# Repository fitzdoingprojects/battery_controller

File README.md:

# battery_controller
battery_controller

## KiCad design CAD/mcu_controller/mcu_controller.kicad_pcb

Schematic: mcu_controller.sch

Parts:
C1, C3: 10uF 50V; C_1206_3216Metric
C2: 0.1uF; C_0603_1608Metric
D1, D3: LED_Small; LED_0603_1608Metric
D2: TL431DBZ; SOT-23
J1: BATT; PhoenixContact_MCV_1,5_2-G-5.08_1x02_P5.08mm_Vertical
J2: BATT_SENSE; PhoenixContact_MCV_1,5_2-G-5.08_1x02_P5.08mm_Vertical
J3: chrg1_vi; PinSocket_1x03_P2.54mm_Vertical
J4: chrg2_vi; PinSocket_1x03_P2.54mm_Vertical
J5: chrg3_vi; PinSocket_1x03_P2.54mm_Vertical
J6: out1_fb; PinSocket_1x05_P2.54mm_Vertical
J7: out2_fb; PinSocket_1x05_P2.54mm_Vertical
J9: out1_ch_en; PinSocket_1x05_P2.54mm_Vertical
J10: out2_ch_en; PinSocket_1x05_P2.54mm_Vertical
J11: SPI; PinSocket_1x05_P2.54mm_Vertical
J12: I2C; PinSocket_1x04_P2.54mm_Vertical
J13: chrg1_ctrl; PinSocket_1x04_P2.54mm_Vertical
J14: chrg2_ctrl; PinSocket_1x04_P2.54mm_Vertical
J15: chrg3_ctrl; PinSocket_1x04_P2.54mm_Vertical
J16: out1_en; PinSocket_1x02_P2.54mm_Vertical
J17: out2_en; PinSocket_1x02_P2.54mm_Vertical
J19: UART; PinSocket_1x04_P2.54mm_Vertical
J20: UEXT; PinSocket_2x05_P2.54mm_Vertical
JP1, JP2: Jumper_NC_Small; SolderJumper-2_P1.3mm_Bridged_RoundedPad1.0x1.5mm
MK1, MK2, MK3, MK4: Mounting_Hole; MountingHole_4.3mm_M4
R1, R2, R24: R; R_0603_1608Metric
R3, R4, R5, R6, R8, R10, R11, R12, R14, R17: 100; R_0603_1608Metric
R7, R9, R15, R18: 100; SolderJumper-2_P1.3mm_Open_RoundedPad1.0x1.5mm
R13, R16, R19, R20, R21, R22, R23, R25, R26, R27, R36: R_Small; R_0603_1608Metric
R28, R29, R30, R31, R32, R33, R34, R35: 1K; SolderJumper-2_P1.3mm_Open_RoundedPad1.0x1.5mm
R37, R38, R39, R40, R41, R42, R43, R44, R45, R46, R47: 1K; R_0603_1608Metric
SW1: SW_SPST; PinSocket_1x02_P2.54mm_Vertical
U1: INA219; SOIC-8_3.9x4.9mm_P1.27mm
U2: AZ1117-ADJ; SOT-223-3_TabPin2
U3: Teensy-LC; Teensy30_31_32_LC

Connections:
+5V: C2.1, C3.1, D1.2, R16.1, R19.1, R21.1, R25.1, R27.1, U1.4, U2.2 (VO), U3.33
/3V3: J11.1, J12.1, J19.1, J20.1, U3.31
/A0: R3.1, U3.21
/A1: R10.2, U3.22
/A2: R4.1, U3.23
/A3: R11.2, U3.24
/A4: JP2.2, U3.25
/A5: JP1.2, U3.26
/A6: R5.1, U3.27
/A7: R12.2, U3.28
/A8: R6.1, U3.29
/A9: R8.1, U3.30
/BATT_IN: J1.2, SW1.1
/BATT_SW: C1.1, R1.1, SW1.2, U2.3 (VI)
/I2C_SCL: J12.2, J20.5, JP1.1, U1.6
/I2C_SDA: J12.3, J20.6, JP2.1, U1.5
/MISO: J11.3, J20.7, U3.14
/MOSI: J11.2, J20.8, U3.13
/RESET: J20.10, U3.18
/RX: J19.3, J20.4, U3.2
/SCK: J11.4, J20.9, U3.20
/TX: J19.2, J20.3, U3.3
/chrg1_en: J13.1, R37.1
/chrg1_i: J3.2, R10.1
/chrg1_v: J3.3, R3.2
/chrg2_en: J14.1, R38.1
/chrg2_i: J4.2, R11.1
/chrg2_v: J4.3, R4.2
/chrg3_en: J15.1, R39.1
/chrg3_i: J5.2, R12.1
/chrg3_v: J5.3, R5.2
/mcu1_set: J13.3, R45.1
/mcu2_set: J14.3, R46.1
/mcu3_set: J15.3, R47.1
/out1_ch1_en: J9.1, R28.1
/out1_ch1_i: J6.1, R6.2
/out1_ch2_en: J9.2, R29.1
/out1_ch2_i: J6.2, R8.2
/out1_ch3_en: J9.3, R30.1
/out1_ch3_i: J6.3, R14.2
/out1_ch4_en: J9.4, R31.1
/out1_ch4_i: J6.4, R17.2
/out1_en: J16.1, R43.1
/out2_ch1_en: J10.1, R32.1
/out2_ch1_i: J7.1, R7.2
/out2_ch2_en: J10.2, R33.1
/out2_ch2_i: J7.2, R9.2
/out2_ch3_en: J10.3, R34.1
/out2_ch3_i: J7.3, R15.2
/out2_ch4_en: J10.4, R35.1
/out2_ch4_i: J7.4, R18.2
/out2_en: J17.1, R44.1
/trickle1_dis: J13.2, R40.1
/trickle2_dis: J14.2, R41.1
/trickle3_dis: J15.2, R42.1
GND: C1.2, C2.2, C3.2, D2.3, J1.1, J3.1, J4.1, J5.1, J6.5, J7.5, J9.5, J10.5, J11.5, J12.4, J13.4, J14.4, J15.4, J16.2, J17.2, J19.4, J20.2, R2.2, R13.1, R20.2, R22.2, R23.2, R26.2, R36.2, U1.3, U3.1, U3.17, U3.32
unnamed: D1.1, R23.1
unnamed: D2.1, R27.2, U3.35
unnamed: D2.2, R25.2, R26.1
unnamed: D3.1, R36.1
unnamed: D3.2, R43.2, R44.2, U3.4
unnamed: J2.1, U1.2
unnamed: J2.2, U1.1
unnamed: R1.2, R2.1, R24.1
unnamed: R13.2, R16.2, U2.1 (ADJ)
unnamed: R14.1, U3.36
unnamed: R17.1, R24.2, U3.37
unnamed: R19.2, R20.1, U1.8
unnamed: R21.2, R22.1, U1.7
unnamed: R37.2, U3.10
unnamed: R38.2, U3.8
unnamed: R39.2, U3.6
unnamed: R40.2, U3.9
unnamed: R41.2, U3.7
unnamed: R42.2, U3.5
unnamed: R45.2, U3.19
unnamed: R46.2, U3.12
unnamed: R47.2, U3.11

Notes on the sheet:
CHARGE CONTROLLER: 2x ADC 1x PWM 2x GPIO
OUTPUT CONTROLLER 4x ADC 1x (5x) GPIO

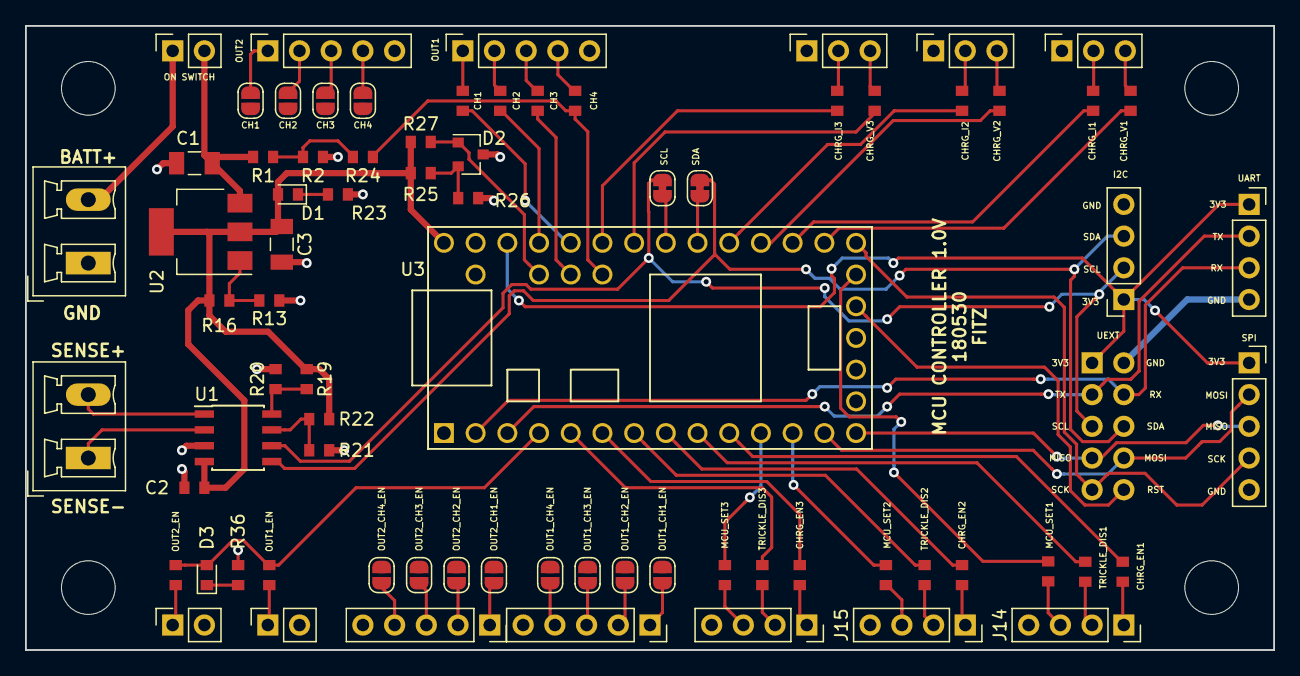
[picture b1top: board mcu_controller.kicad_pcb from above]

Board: 2 copper layers, 100.0 x 50.0 mm, 81 parts (1 on the bottom side), 78 nets.

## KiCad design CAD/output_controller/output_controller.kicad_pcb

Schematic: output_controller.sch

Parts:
C1: 10uF 25V; C_1206_3216Metric
C2, C3, C4, C5: 0.1uF; C_0603_1608Metric
D1: D_Small; D_SOD-523
D2: 12V; D_SOD-523
D3: LED_Small; D_SOD-523
D4, D5, D6, D7: 5V; D_SOD-323_HandSoldering
F1: Fuse; Fuseholder_Blade_Mini_Keystone_3568
J1: 12V_IN; PhoenixContact_MCV_1,5_2-G-5.08_1x02_P5.08mm_Vertical
J2: MCU_SW; PinHeader_1x02_P2.54mm_Vertical
J3: MCU_EN; PinHeader_1x05_P2.54mm_Vertical
J4: MCU_IS; PinHeader_1x05_P2.54mm_Vertical
J5, J6, J7, J8: 12V_A; PhoenixContact_MCV_1,5_2-G-5.08_1x02_P5.08mm_Vertical
MK1, MK2, MK3, MK4: Mounting_Hole; MountingHole_4.3mm_M4
Q1, Q3: Q_PMOS_GDS; TO-252-2
Q2: MMBT3904; SOT-23
Q4, Q5, Q6, Q7: AO3400; SOT-23
R1, R10, R11, R12, R13, R27, R29, R31, R33: 10K; R_0603_1608Metric
R2, R3, R5, R6, R7, R8, R9, R14, R15, R16, R17, R18, R19, R20, R21, R22, R23, R24, R25, R26, R28, R30, R32, R34: 1K; R_0603_1608Metric
R4: 470K; R_0603_1608Metric
SW1: EN; PinHeader_1x02_P2.54mm_Vertical
SW2, SW3, SW4, SW5: SW_Push_LED; PinHeader_1x04_P2.54mm_Vertical
U1, U2, U3, U4: BTS443P; TO-252-4

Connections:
/IN1: R15.1, U1.2 (IN)
/IN2: R16.1, U2.2 (IN)
/IN3: R17.1, U3.2 (IN)
/IN4: R18.1, U4.2 (IN)
/IN_SW1: C2.1, Q4.3, R15.2, SW2.2
/IN_SW2: C3.1, Q5.3, R16.2, SW3.2
/IN_SW3: C4.1, Q6.3, R17.2, SW4.2
/IN_SW4: C5.1, Q7.3, R18.2, SW5.2
/IS1: R23.1, R27.2, R28.2, U1.4 (IS)
/IS2: R24.1, R29.2, R30.2, U2.4 (IS)
/IS3: R25.1, R31.2, R32.2, U3.4 (IS)
/IS4: R26.1, R33.2, R34.2, U4.4 (IS)
/OUT1: J5.1, R19.2, U1.1 (OUT), U1.5 (OUT)
/OUT2: J6.1, R20.1, U2.1 (OUT), U2.5 (OUT)
/OUT3: J7.1, R21.2, U3.1 (OUT), U3.5 (OUT)
/OUT4: J8.1, R22.2, U4.1 (OUT), U4.5 (OUT)
/VBB: D3.2, Q3.2, U1.3 (Vbb), U2.3 (Vbb), U3.3 (Vbb), U4.3 (Vbb)
/VIN: F1.2, J1.2
/VIN_FUSED: C1.1, F1.1, Q1.2, SW1.1
/VIN_VBB: D2.1, Q1.3, Q3.3, R4.1
/ch1_en: J3.5, R6.2
/ch1_i: J4.1, R27.1
/ch2_en: J3.4, R7.2
/ch2_i: J4.2, R29.1
/ch3_en: J3.3, R8.2
/ch3_i: J4.3, R31.1
/ch4_en: J3.2, R9.2
/ch4_i: J4.4, R33.1
/out_en: D1.2, J2.1
GND: C1.2, C2.2, C3.2, C4.2, C5.2, D4.2, D5.2, D6.2, D7.2, J1.1, J2.2, J3.1, J4.5, J5.2, J6.2, J7.2, J8.2, Q2.2 (E), Q4.2, Q5.2, Q6.2, Q7.2, R3.2, R10.2, R11.2, R12.2, R13.2, R14.2, R23.2, R24.2, R25.2, R26.2, SW2.1, SW2.3, SW3.1, SW3.3, SW4.1, SW4.3, SW5.1, SW5.3
unnamed: D1.1, R1.2, R2.2
unnamed: D2.2, Q1.1, Q3.1, R4.2, R5.1
unnamed: D3.1, R14.1
unnamed: D4.1, R28.1
unnamed: D5.1, R30.1
unnamed: D6.1, R32.1
unnamed: D7.1, R34.1
unnamed: Q2.1 (B), R2.1, R3.1
unnamed: Q2.3 (C), R5.2
unnamed: Q4.1, R6.1, R10.1
unnamed: Q5.1, R7.1, R11.1
unnamed: Q6.1, R8.1, R12.1
unnamed: Q7.1, R9.1, R13.1
unnamed: R1.1, SW1.2
unnamed: R19.1, SW2.4
unnamed: R20.2, SW3.4
unnamed: R21.1, SW4.4
unnamed: R22.1, SW5.4

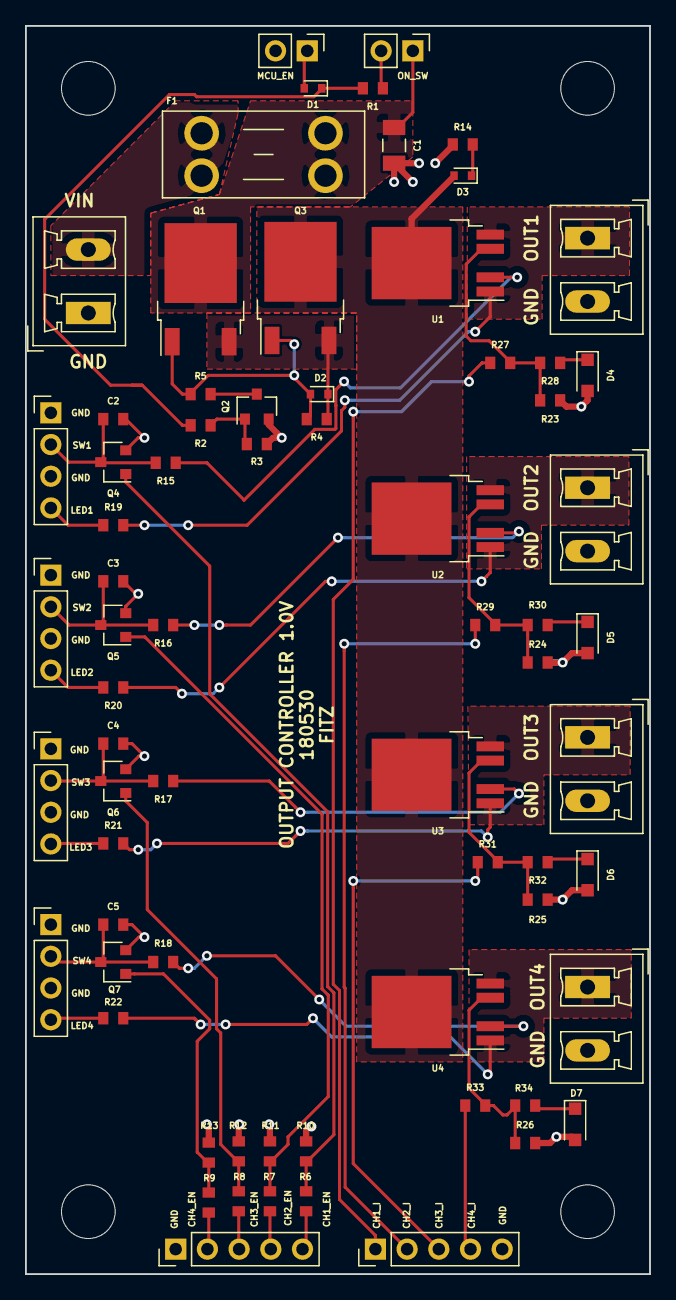
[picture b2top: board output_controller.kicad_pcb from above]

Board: 2 copper layers, 50.0 x 100.0 mm, 75 parts (0 on the bottom side), 48 nets.

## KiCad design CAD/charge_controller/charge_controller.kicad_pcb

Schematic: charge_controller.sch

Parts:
C1, C2, C5, C6: 10uF 25V; C_1210_3225Metric
C3: C_Small; C_0603_1608Metric
C4, C9: NC; C_0603_1608Metric
C7, C8, C21: 0.1uF; C_0603_1608Metric
D1: TL431DBZ; SOT-23
D2, D3, D7: D_Schottky; D_SOD-523
D4: 1N4148; D_SOD-523
D5, D6: 12V; D_SOD-523
F1: Fuse; Fuseholder_Blade_Mini_Keystone_3568
J1: MCU; PinSocket_1x04_P2.54mm_Vertical
J2: PSU; PhoenixContact_MCV_1,5_2-G-5.08_1x02_P5.08mm_Vertical
J3, J6: Conn_02x03_Odd_Even; PinHeader_2x03_P2.54mm_Vertical_SMD
J4: BATT; PhoenixContact_MCV_1,5_2-G-5.08_1x02_P5.08mm_Vertical
J5: FB; PhoenixContact_MCV_1,5_3-G-5.08_1x03_P5.08mm_Vertical
J7: CHARGE_VI; PinSocket_1x03_P2.54mm_Vertical
JP1: DEFAULT_EN; SolderJumper-2_P1.3mm_Open_RoundedPad1.0x1.5mm
JP3, JP4: vref; SolderJumper-2_P1.3mm_Bridged_Pad1.0x1.5mm
L1: L_Small; L_0603_1608Metric
L10: JUMPER; SolderJumper-2_P1.3mm_Bridged_Pad1.0x1.5mm
MK1, MK2, MK3, MK4: Mounting_Hole; MountingHole_4.3mm_M4
Q1, Q5: Q_NMOS_SDG; SOT-23
Q2, Q4: Q_PMOS_GDS; TO-252-2
Q3: MMBT3904; SOT-23
R1, R2, R4, R5, R8, R9, R10, R11, R29, R31, R34: 56K; R_0603_1608Metric
R3, R13, R28, R38: 10K; R_0603_1608Metric
R6, R26, R27, R37: 1K; R_0603_1608Metric
R7: 470K; R_0603_1608Metric
R12: 100K; R_0603_1608Metric
R14, R15, R16, R18, R19, R20, R22, R23, R24: R_Small; R_0603_1608Metric
R17, R47: 20K; R_0603_1608Metric
R21, R30: NC; R_0603_1608Metric
R25: 100; R_0603_1608Metric
R32, R33, R35, R36: 0.1R; R_1206_3216Metric
U1: LMV324; SOIC-14_3.9x8.7mm_P1.27mm
U2: L7812; TO-252-2

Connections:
+12V: C21.2, L10.1, R4.1, R8.1, R9.1, R47.1, U1.4 (V+)
+BATT: C5.2, C6.2, J4.1, Q4.2, R12.1
+VDC: C1.2, F1.1, Q2.2, R13.2, R27.1, U2.1 (IN)
/12V_O: C2.2, L10.2, U2.3 (OUT)
/BATT_SENSE: C5.1, C6.1, J4.2, R32.1, R33.1, R35.1, R36.1, U1.3 (+)
/BOOST_FB: D2.1, D3.1, D7.1, J5.2
/VIN: F1.2, J2.2
/VIN_BATT: D5.1, Q2.3, Q4.3, R7.1
/V_ref: JP3.2, R15.1, R16.1, R19.1, R26.1
/batt_v: JP4.2, R23.1
/chrg_en: D4.2, J1.1
/chrg_i: J7.2, R2.1, R30.1, U1.1
/chrg_in_v: J5.1, R38.2
/chrg_v: J7.1, R37.1, R38.1
/mcu_set: J1.3, R29.1
/trickle_dis: J1.2, R18.2
GND: C1.1, C2.1, C3.1, C8.2, C9.1, C21.1, D1.3, D6.2, J1.4, J2.1, J5.3, J7.3, Q1.1, Q3.2 (E), Q5.1, R1.2, R3.1, R5.2, R10.2, R11.2, R20.2, R22.2, R24.2, R28.1, R31.2, R32.2, R33.2, R35.2, R36.2, R37.2, U1.11 (V-), U2.2 (GND)
unnamed: C3.2, R15.2, R22.1, U1.9 (-)
unnamed: C4.1, D3.2, U1.7
unnamed: C4.2, R21.2
unnamed: C7.1, Q5.2, R17.2
unnamed: C7.2, JP4.1, R12.2, R17.1
unnamed: C8.1, L1.2, U1.12 (+)
unnamed: C9.2, R31.1, R34.2, U1.13 (-)
unnamed: D1.1, JP3.1, R47.2
unnamed: D1.2, J3.2, J3.4, J3.6
unnamed: D2.2, U1.8
unnamed: D4.1, JP1.2, R3.2, R6.1
unnamed: D5.2, Q2.1, Q4.1, R7.2, R25.1
unnamed: D6.1, Q5.3, R27.2, R28.2
unnamed: D7.2, R34.1, U1.14
unnamed: J3.1, R8.2, R11.1
unnamed: J3.3, R9.2, R10.1
unnamed: J3.5, R4.2, R5.1
unnamed: J6.1, J6.3, J6.5, R14.1, R20.1, U1.6 (-)
unnamed: J6.2, R19.2
unnamed: J6.4, R26.2
unnamed: J6.6, R16.2
unnamed: JP1.1, R13.1
unnamed: L1.1, R29.2
unnamed: Q1.2, R14.2
unnamed: Q1.3, R18.1, R24.1
unnamed: Q3.1 (B), R6.2
unnamed: Q3.3 (C), R25.2
unnamed: R1.1, R2.2, U1.2 (-)
unnamed: R21.1, R30.2, U1.5 (+)
unnamed: R23.2, U1.10 (+)

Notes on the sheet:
Optional Filtering
Trickle Charge DISABLE
REF = Battery Voltage / 6
CURRENT SENSE AMPLIFIER
OVER CURRENT PROTECTION
OVER VOLTAGE PROTECTION
MCU CHARGE CONTROL
GND close to sense resistors
MUST CONNECT TO FB PIN AND INPUT VOLTAGE ON BOOST CONVERTER

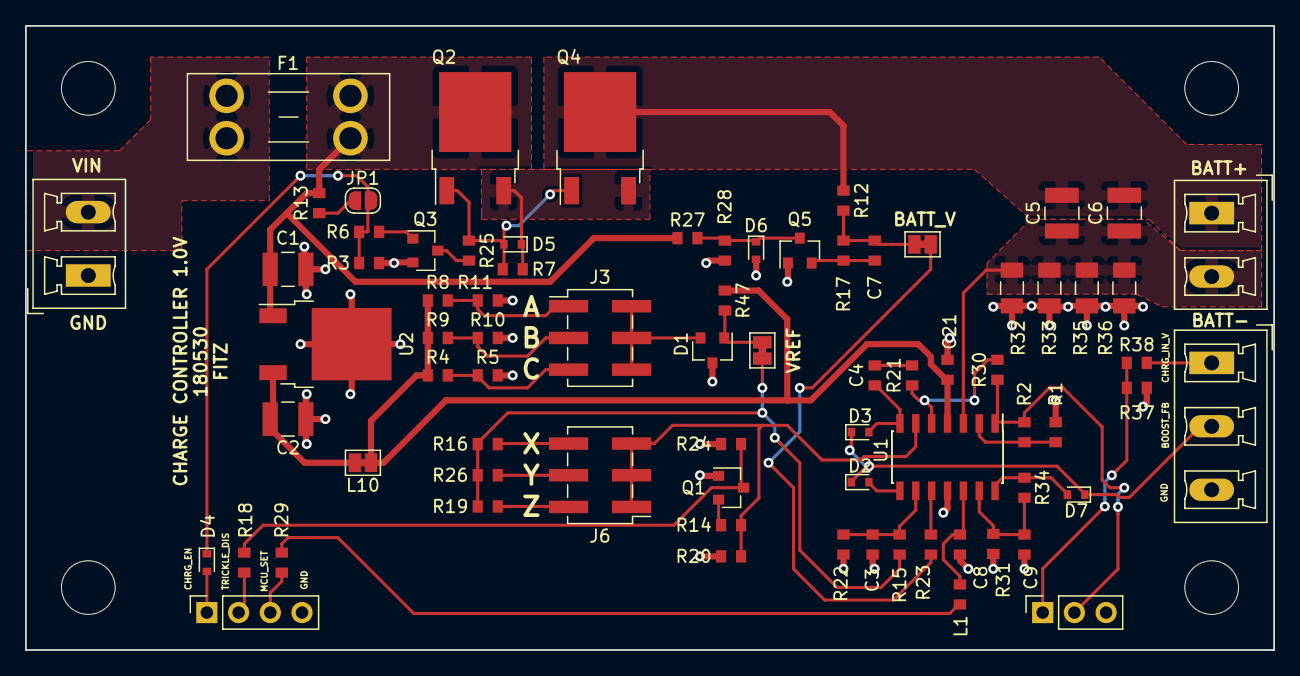
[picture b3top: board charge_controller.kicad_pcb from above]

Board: 2 copper layers, 100.0 x 50.0 mm, 80 parts (0 on the bottom side), 47 nets.

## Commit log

2018-05-03 saves before revision to charge circuit
2018-05-24 major changes
2018-05-24 finishes mcu controller schematic
2018-05-27 progress on charge and output layout
2018-05-28 finishes output board
2018-05-31 finishes layout for mcu controller
2018-05-31 finishes output controller
2018-05-31 removes pin 17 connection to VIN on mcu controller
2018-06-04 final commit before seeed, adds GERBERs
